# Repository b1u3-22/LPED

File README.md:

# LPED

Highly customizable Low-power Electronic Playing Dice

> This project started as a bachelors thesis, the original repository can be found [here](https://git.fit.vutbr.cz/xsedla2e/BP-LPED)

## Features

* Separate charging station for charging the dice via pogo-pins
* Changing the dice shape with custom sleeves 
* The dice can be configured to support any shape with up to 60 sides
* Up to 10 profiles can be saved onboard 

### Hardware 

* The dice uses a nRF52833 microcontroller with FXLS8974CF accelerometer
* Instead of battery it uses hybrid super-capacitor with 20 F capacity that provides up to 8 hours of game time with charging time of 15 minutes
* RGB LED on-board the dice
* The charger has separate battery providing up to two full dice charges
* The 3D models of the charging dock have been optimized for 3D printing and they do not require any supports
	* However, one heat inserts and 4 magnets (6x6x2mm) are necessary for the assembly

### Firmware 

* The dice transmits the landed numbers via BLE broadcast advertisement
	* To ensure they get to the client application, they are sent multiple times with unique identifier
* For configuration it is necessary to connect to the dice
	* It provides all the necessary parameters via characteristics in custom GATT service
* It saves the whole configuration in the FLASH memory of the dice, making it independent on the used client application
* Each side can have its own physical position on the dice and its own number, making it possible to create dice with custom non-standard shapes

## Project structure 
* `/hardware` - schematics, 3D models and PCB design files for dice, charger and programming adapter
	* The schematics and PCB designs were made in KiCad 
	* The printable models were made in FreeCAD 
* `/firmware` - Zephyr firmware running on the dice

## Versioning info 
* Repository uses `major.minor` format
	* `major` is incremented with each major hardware revision or significant firmware update that causes the implementation to be incompatible with previous version
	* `minor` is used for firmware fixes and patches that don't affect backwards compatibility
	* Branch names are created based on major revisions 
* PCBs have their own version code on them that follows standard `major.minor` format
	* `major` is used for drastic changes to the boards, such as MCU swap or change of pinout
	* `minor` is used for hardware fixes and patches

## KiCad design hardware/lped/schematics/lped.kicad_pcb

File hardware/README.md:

# Hardware designs 
* Schematic, PCB design files and used 3D models used in the design for the die, charging dock and programming adapter
* The `complete_bom.csv` contains BOM with components selected from Mouser

## Structure
1. `lped`
    * Design files for the die
2. `lped_dock`
    * Design files for for the modular charging station and single dice charging station
3. `lped_prog`
    * Design files for the programming adapter
2. `3d_models`
    * 3D models used in PCB design files in all three boards

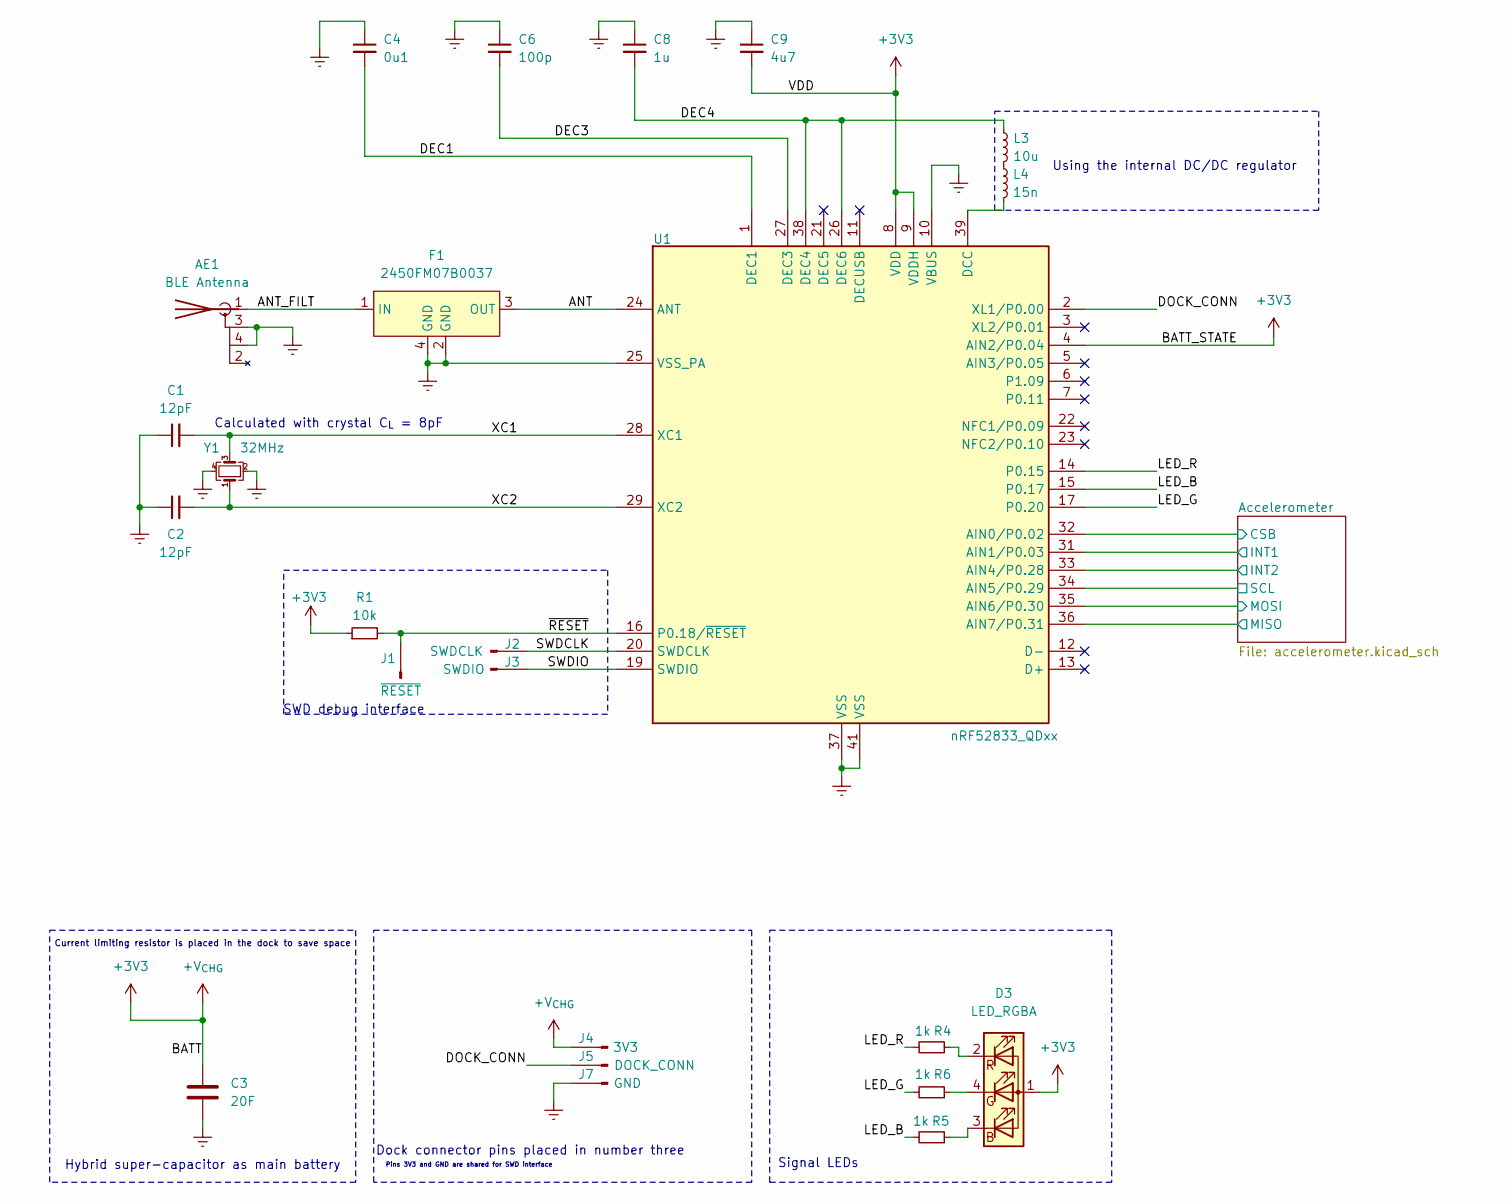
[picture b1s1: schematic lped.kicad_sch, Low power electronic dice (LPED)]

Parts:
AE1: BLE Antenna; XDCR_2450AT42E010BE
C1, C2: 12pF; C_0402_1005Metric
C3: 20F; C_Radial_D8.0mm_H11.5mm_P3.50mm
C4: 0u1; C_0402_1005Metric
C6: 100p; C_0402_1005Metric
C8: 1u; C_0603_1608Metric
C9: 4u7; C_0603_1608Metric
D3: LED_RGBA; LED_Wurth_150044M155260
F1: 2450FM07B0037; FIL_2450FM07D0034T
J1: ~{RESET}; TestPoint_Pad_D2.0mm
J2: SWDCLK; TestPoint_Pad_D2.0mm
J3: SWDIO; TestPoint_Pad_D2.0mm
J4: 3V3; TestPoint_Pad_D2.0mm
J5: DOCK_CONN; TestPoint_Pad_D2.0mm
J7: GND; TestPoint_Pad_2.0x2.0mm
L3: 10u; L_0603_1608Metric
L4: 15n; L_0402_1005Metric
R1: 10k; R_0402_1005Metric
R4, R5, R6: 1k; R_0402_1005Metric
U1: nRF52833_QDxx; QFN-40-1EP_5x5mm_P0.4mm_EP3.6x3.6mm
Y1: 32MHz; Crystal_SMD_2016-4Pin_2.0x1.6mm

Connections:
+3V3: C3.1, C9.2, D3.1 (A), J4.1, R1.1, U1.4 (AIN2/P0.04), U1.8 (VDD), U1.9 (VDDH), U1.18 (VDD), U1.30 (VDD), U1.40 (VDD); also elsewhere on the board
/ANT: F1.3 (OUT), U1.24 (ANT)
/ANT_FILT: AE1.1 (A), F1.1 (IN)
/Accelerometer/CSB: U1.32 (AIN0/P0.02); also elsewhere on the board
/Accelerometer/INT1: U1.31 (AIN1/P0.03); also elsewhere on the board
/Accelerometer/INT2: U1.33 (AIN4/P0.28); also elsewhere on the board
/Accelerometer/MISO: U1.36 (AIN7/P0.31); also elsewhere on the board
/Accelerometer/MOSI: U1.35 (AIN6/P0.30); also elsewhere on the board
/Accelerometer/SCL: U1.34 (AIN5/P0.29); also elsewhere on the board
/DEC1: C4.2, U1.1 (DEC1)
/DEC3: C6.2, U1.27 (DEC3)
/DEC4: C8.2, L3.1, U1.26 (DEC6), U1.38 (DEC4)
/DOCK_CONN: J5.1, U1.2 (XL1/P0.00)
/LED_B: R5.2, U1.15 (P0.17)
/LED_G: R6.2, U1.17 (P0.20)
/LED_R: R4.2, U1.14 (P0.15)
/SWDCLK: J2.1, U1.20 (SWDCLK)
/SWDIO: J3.1, U1.19 (SWDIO)
/XC1: C1.2, U1.28 (XC1), Y1.3
/XC2: C2.2, U1.29 (XC2), Y1.1
/~RESET: J1.1, R1.2, U1.16 (P0.18/~RESET)
Earth: AE1.3 (Shield), AE1.4 (Shield), C1.1, C2.1, C3.2, C4.1, C6.1, C8.1, C9.1, F1.2 (GND), F1.4 (GND), J7.1, U1.10 (VBUS), U1.25 (VSS_PA), U1.37 (VSS), U1.41 (VSS), Y1.2, Y1.4; also elsewhere on the board
unnamed: D3.3 (BK), R5.1
unnamed: D3.4 (GK), R6.1
unnamed: D3.2 (RK), R4.1
unnamed: L3.2, L4.1
unnamed: L4.2, U1.39 (DCC)

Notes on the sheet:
Calculated with crystal C_{L} = 8pF
SWD debug interface
Current limiting resistor is placed in the dock to save space
Signal LEDs
Dock connector pins placed in number three
Hybrid super-capacitor as main battery
Using the internal DC/DC regulator
Pins 3V3 and GND are shared for SWD interface

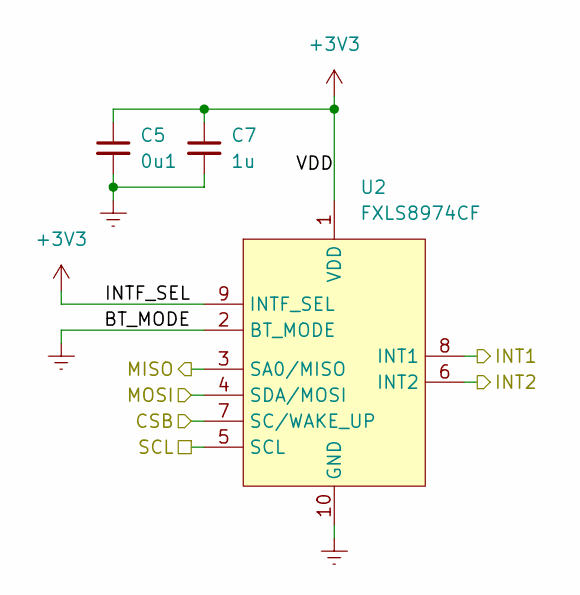
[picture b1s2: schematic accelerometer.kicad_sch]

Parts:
C5: 0u1; C_0402_1005Metric
C7: 1u; C_0402_1005Metric
U2: FXLS8974CF; DFN-10_2x2mm_P0.4mm

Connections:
+3V3: C5.1, C7.1, U2.1 (VDD), U2.9 (INTF_SEL); also elsewhere on the board
/Accelerometer/CSB: U2.7 (SC/WAKE_UP); also elsewhere on the board
/Accelerometer/INT1: U2.8 (INT1); also elsewhere on the board
/Accelerometer/INT2: U2.6 (INT2); also elsewhere on the board
/Accelerometer/MISO: U2.3 (SA0/MISO); also elsewhere on the board
/Accelerometer/MOSI: U2.4 (SDA/MOSI); also elsewhere on the board
/Accelerometer/SCL: U2.5 (SCL); also elsewhere on the board
Earth: C5.2, C7.2, U2.2 (BT_MODE), U2.10 (GND); also elsewhere on the board

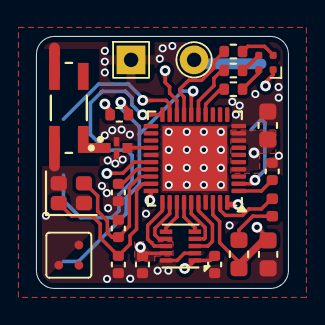
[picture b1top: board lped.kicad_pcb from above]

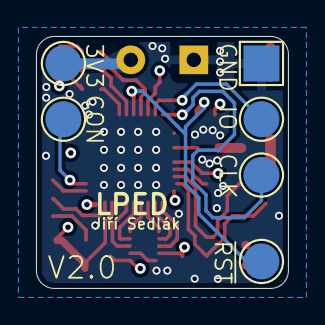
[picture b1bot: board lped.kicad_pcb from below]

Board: 4 copper layers, 14.0 x 14.0 mm, 27 parts (6 on the bottom side), 27 nets.

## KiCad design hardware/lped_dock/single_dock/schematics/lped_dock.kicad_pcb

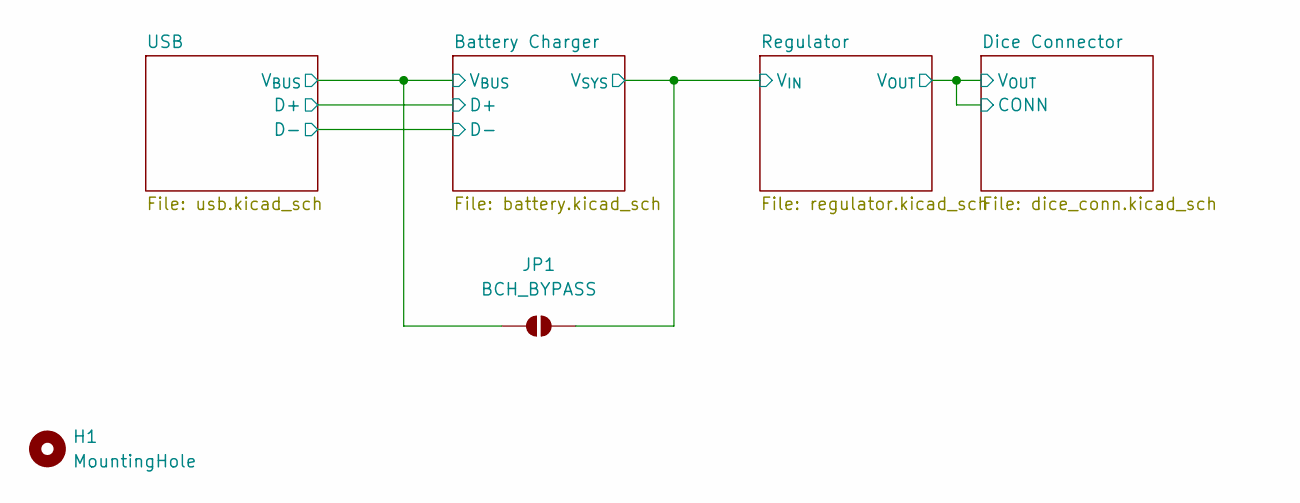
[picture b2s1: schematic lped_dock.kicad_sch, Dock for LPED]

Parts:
H1: MountingHole; MountingHole_3.2mm_M3
JP1: BCH_BYPASS; SolderJumper-2_P1.3mm_Open_Pad1.0x1.5mm

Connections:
/Battery Charger/V_{BUS}: JP1.1 (A); also elsewhere on the board
/Battery Charger/V_{SYS}: JP1.2 (B); also elsewhere on the board

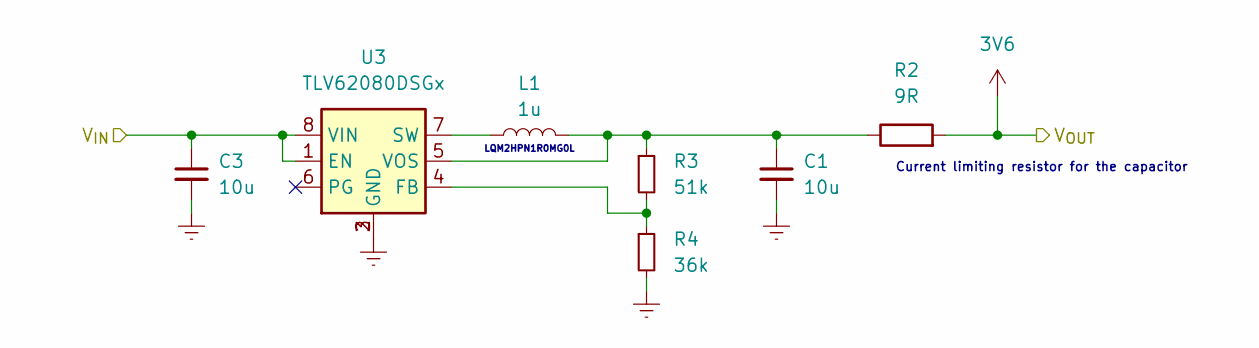
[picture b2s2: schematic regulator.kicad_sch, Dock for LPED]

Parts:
C1, C3: 10u; C_0603_1608Metric
L1: 1u; L_1008_2520Metric
R2: 9R; R_2512_6332Metric
R3: 51k; R_0402_1005Metric
R4: 36k; R_0402_1005Metric
U3: TLV62080DSGx; WSON-8-1EP_2x2mm_P0.5mm_EP0.9x1.6mm

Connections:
3V6: R2.2; also elsewhere on the board
/Battery Charger/V_{SYS}: C3.1, U3.1 (EN), U3.8 (VIN); also elsewhere on the board
Earth: C1.2, C3.2, R4.2, U3.2 (GND), U3.3 (GND), U3.9 (GND); also elsewhere on the board
unnamed: R3.2, R4.1, U3.4 (FB)
unnamed: L1.1, U3.7 (SW)
unnamed: C1.1, L1.2, R2.1, R3.1, U3.5 (VOS)

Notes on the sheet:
Current limiting resistor for the capacitor
LQM2HPN1R0MG0L

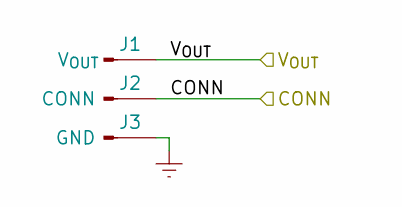
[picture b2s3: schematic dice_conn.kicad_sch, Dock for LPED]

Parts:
J1: V_{OUT}; Pin_D0.9mm_L10.0mm_W2.4mm_FlatFork
J2: CONN; Pin_D0.9mm_L10.0mm_W2.4mm_FlatFork
J3: GND; Pin_D0.9mm_L10.0mm_W2.4mm_FlatFork

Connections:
3V6: J1.1, J2.1; also elsewhere on the board
Earth: J3.1; also elsewhere on the board

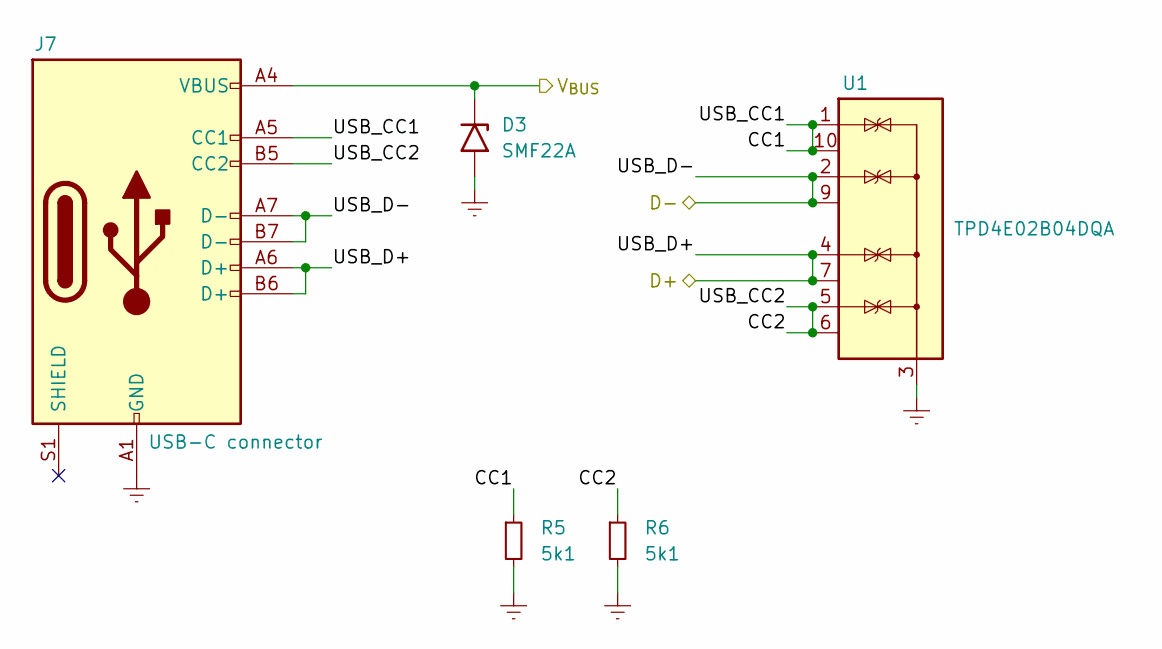
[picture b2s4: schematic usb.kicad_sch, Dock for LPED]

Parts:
D3: SMF22A; D_SOD-123
J7: USB-C connector; USB_C_Receptacle_GCT_USB4105-xx-A_16P_TopMnt_Horizontal
R5, R6: 5k1; R_0402_1005Metric
U1: TPD4E02B04DQA; USON-10_2.5x1.0mm_P0.5mm

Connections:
/Battery Charger/V_{BUS}: D3.1 (A1), J7.A4 (VBUS), J7.A9 (VBUS), J7.B4 (VBUS), J7.B9 (VBUS); also elsewhere on the board
/USB/CC1: J7.A5 (CC1), R5.1, U1.1 (IO1), U1.10 (NC)
/USB/CC2: J7.B5 (CC2), R6.1, U1.5 (IO4), U1.6 (NC)
/USB/USB_D+: J7.A6 (D+), J7.B6 (D+), U1.4 (IO3), U1.7 (NC); also elsewhere on the board
/USB/USB_D-: J7.A7 (D-), J7.B7 (D-), U1.2 (IO2), U1.9 (NC); also elsewhere on the board
Earth: D3.2 (A2), J7.A1 (GND), J7.A12 (GND), J7.B1 (GND), J7.B12 (GND), R5.2, R6.2, U1.3 (G), U1.8 (G); also elsewhere on the board

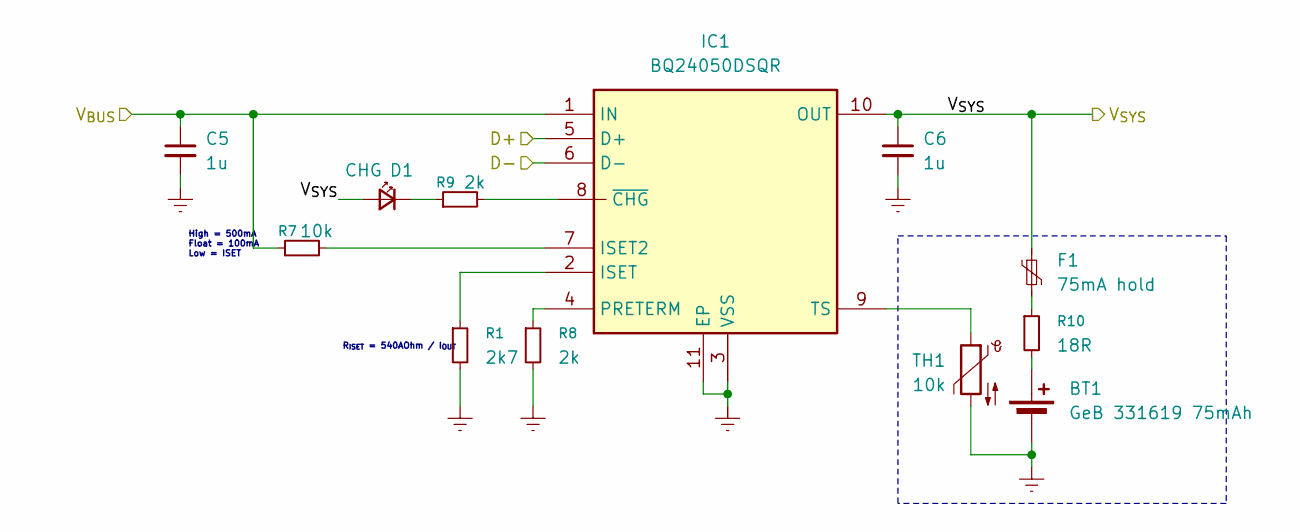
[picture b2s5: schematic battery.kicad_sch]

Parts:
BT1: GeB 331619 75mAh; JST_PH_S2B-PH-K_1x02_P2.00mm_Horizontal
C5, C6: 1u; C_0603_1608Metric
D1: CHG; LED_0805_2012Metric
F1: 75mA hold; Fuse_1206_3216Metric
IC1: BQ24050DSQR; SON40P200X200X80-11N; Manufacturer_Part_Number BQ24050DSQR; Mouser Part Number 595-BQ24050DSQR
R1: 2k7; R_0402_1005Metric
R7: 10k; R_0402_1005Metric
R8, R9: 2k; R_0402_1005Metric
R10: 18R; R_1206_3216Metric
TH1: 10k; R_0402_1005Metric

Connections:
/Battery Charger/V_{BUS}: C5.1, IC1.1 (IN), R7.1; also elsewhere on the board
/Battery Charger/V_{SYS}: C6.1, D1.2 (A), F1.1, IC1.10 (OUT); also elsewhere on the board
/USB/USB_D+: IC1.5 (D+); also elsewhere on the board
/USB/USB_D-: IC1.6 (D-); also elsewhere on the board
Earth: BT1.2 (-), C5.2, C6.2, IC1.3 (VSS), IC1.11 (EP), R1.2, R8.2, TH1.2; also elsewhere on the board
unnamed: BT1.1 (+), R10.2
unnamed: D1.1 (K), R9.1
unnamed: F1.2, R10.1
unnamed: IC1.7 (ISET2), R7.2
unnamed: IC1.2 (ISET), R1.1
unnamed: IC1.4 (PRETERM), R8.1
unnamed: IC1.9 (TS), TH1.1
unnamed: IC1.8 (~CHG), R9.2

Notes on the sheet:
High = 500mA Float = 100mA Low = ISET
R_{ISET} = 540AOhm / I_{OUT}

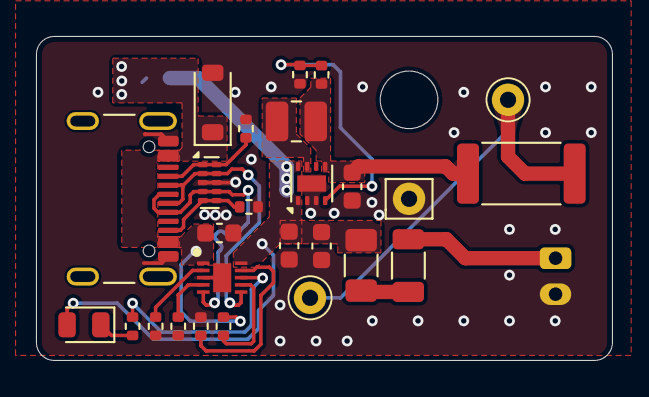
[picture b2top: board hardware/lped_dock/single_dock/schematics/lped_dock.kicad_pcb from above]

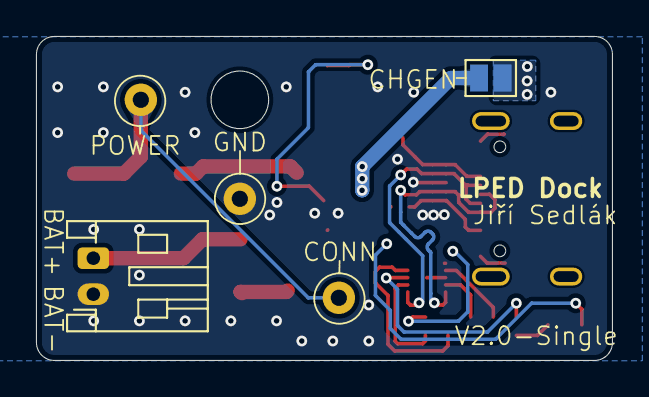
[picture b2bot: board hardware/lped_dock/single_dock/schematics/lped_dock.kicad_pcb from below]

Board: 2 copper layers, 32.0 x 18.0 mm, 29 parts (2 on the bottom side), 19 nets.

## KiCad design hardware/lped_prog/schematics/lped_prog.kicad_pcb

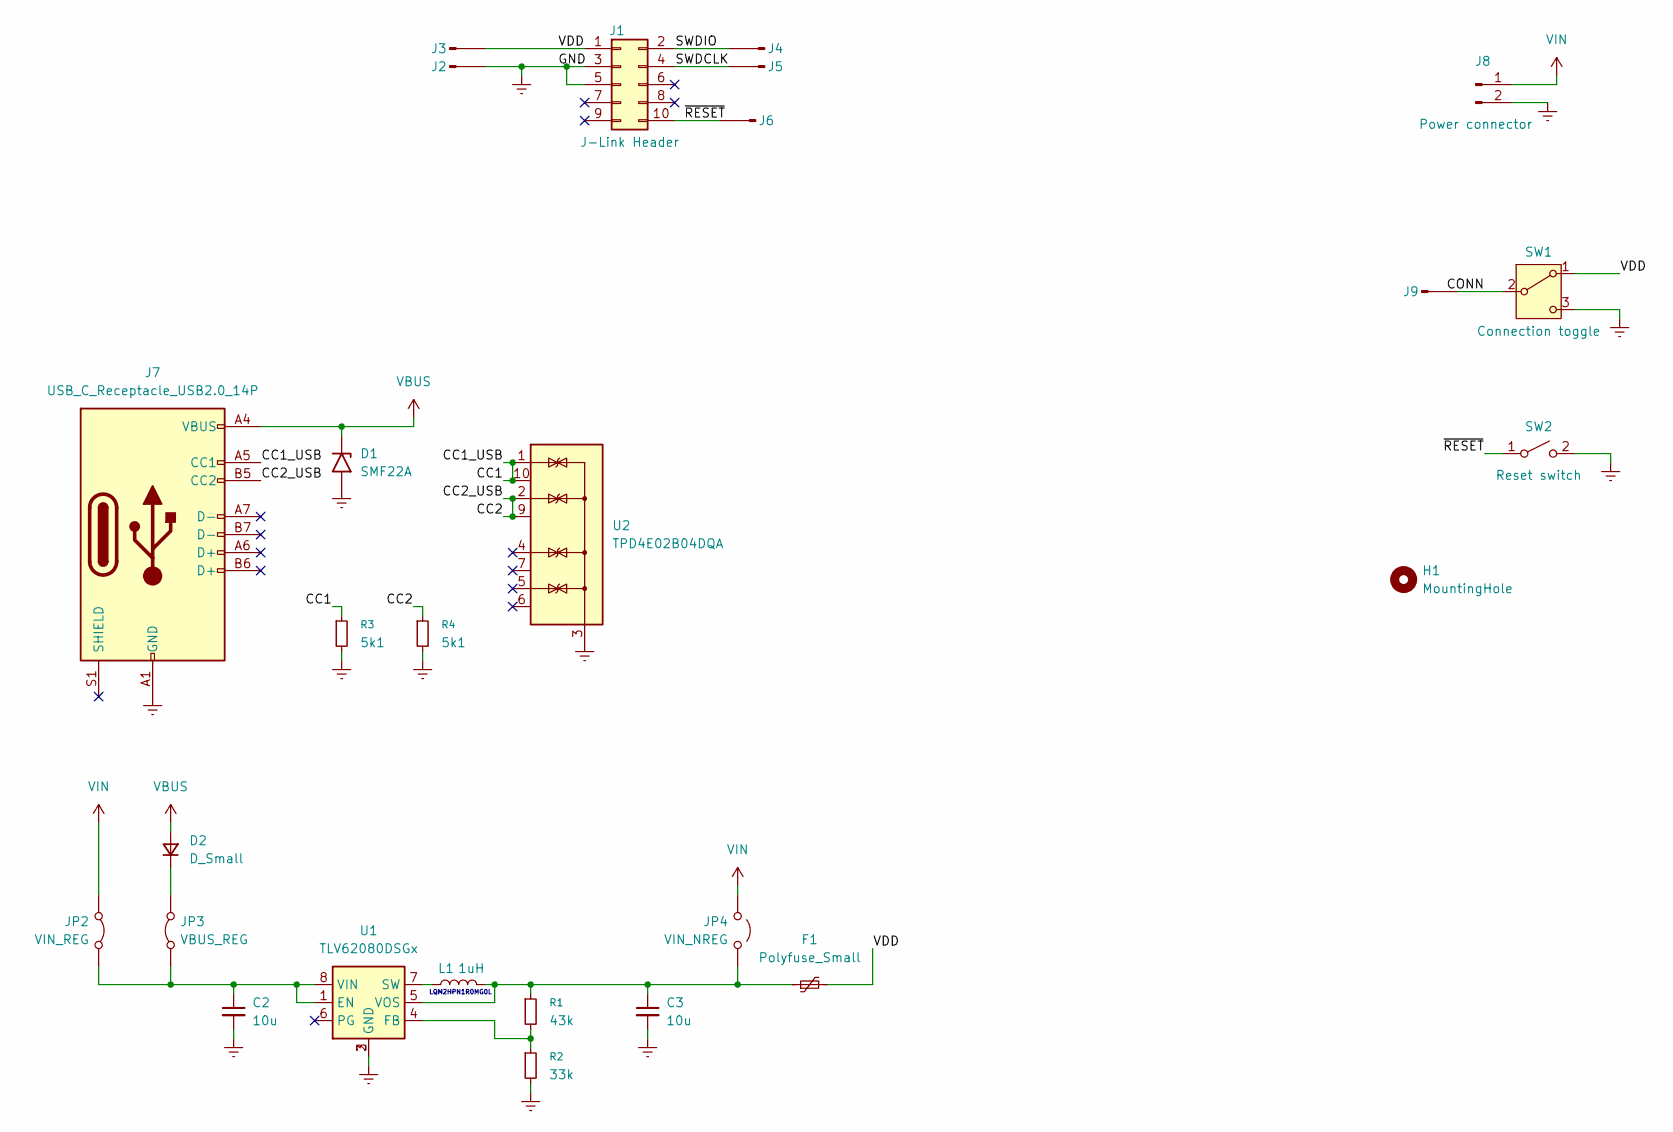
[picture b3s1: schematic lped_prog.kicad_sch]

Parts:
C2, C3: 10u; C_0603_1608Metric
D1: SMF22A; D_SMF
D2: D_Small; D_SOD-123F
F1: Polyfuse_Small; Fuse_1206_3216Metric
H1: MountingHole; MountingHole_3.2mm_M3
J1: J-Link Header; PinHeader_2x05_P1.27mm_Vertical_SMD
J2, J3, J4, J5, J6, J9: Conn_01x01_Pin; Pin_D0.9mm_L10.0mm_W2.4mm_FlatFork
J7: USB_C_Receptacle_USB2.0_14P; USB_C_Receptacle_GCT_USB4105-xx-A_16P_TopMnt_Horizontal
J8: Power connector; PinHeader_1x02_P2.54mm_Vertical
JP2: VIN_REG; PinHeader_1x02_P2.54mm_Vertical
JP3: VBUS_REG; PinHeader_1x02_P2.54mm_Vertical
JP4: VIN_NREG; PinHeader_1x02_P2.54mm_Vertical
L1: 1uH; L_1008_2520Metric
R1: 43k; R_0402_1005Metric
R2: 33k; R_0402_1005Metric
R3, R4: 5k1; R_0402_1005Metric
SW1: Connection toggle; EG1215AA
SW2: Reset switch; SW_PUSH_6mm_H4.3mm
U1: TLV62080DSGx; WSON-8-1EP_2x2mm_P0.5mm_EP0.9x1.6mm
U2: TPD4E02B04DQA; USON-10_2.5x1.0mm_P0.5mm

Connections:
/CC1: J7.A5 (CC1), R3.1, U2.1 (IO1), U2.10 (NC)
/CC2: J7.B5 (CC2), R4.1, U2.2 (IO2), U2.9 (NC)
/CONN: J9.1, SW1.2 (B)
/SWDCLK: J1.4, J5.1
/SWDIO: J1.2, J4.1
/VDD: F1.2, J1.1, J3.1, SW1.1 (A)
/~RESET: J1.10, J6.1, SW2.1 (A)
Earth: C2.2, C3.2, D1.2 (A2), J1.3, J1.5, J2.1, J7.A1 (GND), J7.A12 (GND), J7.B1 (GND), J7.B12 (GND), J8.2, R2.2, R3.2, R4.2, SW1.3 (C), SW2.2 (B), U1.2 (GND), U1.3 (GND), U1.9 (GND), U2.3 (G), U2.8 (G)
unnamed: D2.1 (K), JP3.2 (B)
unnamed: C2.1, JP2.1 (A), JP3.1 (A), U1.1 (EN), U1.8 (VIN)
unnamed: C3.1, F1.1, JP4.1 (A), L1.2, R1.1, U1.5 (VOS)
unnamed: R1.2, R2.1, U1.4 (FB)
unnamed: L1.1, U1.7 (SW)
VBUS: D1.1 (A1), D2.2 (A), J7.A4 (VBUS), J7.A9 (VBUS), J7.B4 (VBUS), J7.B9 (VBUS)
VIN: J8.1, JP2.2 (B), JP4.2 (B)

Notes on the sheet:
LQM2HPN1R0MG0L

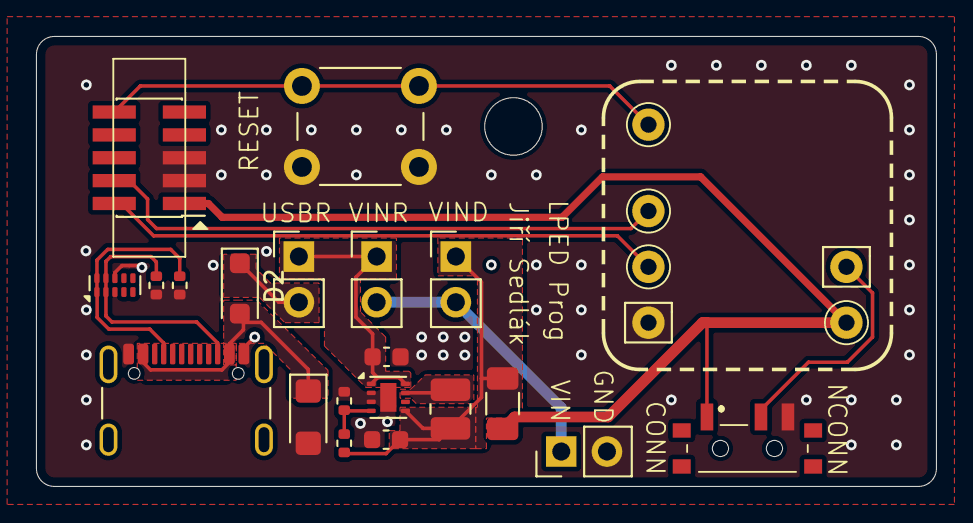
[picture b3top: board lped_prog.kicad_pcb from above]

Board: 2 copper layers, 50.0 x 25.0 mm, 27 parts (0 on the bottom side), 15 nets.

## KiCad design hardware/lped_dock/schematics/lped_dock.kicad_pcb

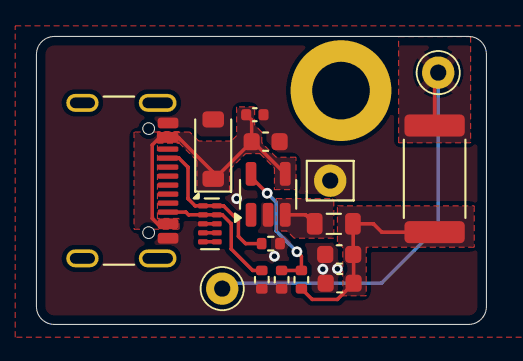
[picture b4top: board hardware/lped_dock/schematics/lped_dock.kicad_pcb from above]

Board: 2 copper layers, 25.0 x 16.0 mm, 18 parts (0 on the bottom side), 10 nets.

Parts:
C1, C2, C3: 10u; C_0603_1608Metric
C4: 0u1; C_0402_1005Metric
D3: SMF22A; D_SOD-123
H1: M3; MountingHole_3.2mm_M3_DIN965_Pad
J1: V_{OUT}; Pin_D0.9mm_L10.0mm_W2.4mm_FlatFork
J2: CONN; Pin_D0.9mm_L10.0mm_W2.4mm_FlatFork
J3: GND; Pin_D0.9mm_L10.0mm_W2.4mm_FlatFork
J7: USB-C connector; USB_C_Receptacle_GCT_USB4105-xx-A_16P_TopMnt_Horizontal
L1: 10u; L_0805_2012Metric
R2: 9R; R_2512_6332Metric
R3: 77k; R_0402_1005Metric
R4: 22k; R_0402_1005Metric
R5, R6: 5k1; R_0402_1005Metric
U1: TPD4E02B04DQA; USON-10_2.5x1.0mm_P0.5mm
U2: TPS560200; SOT-23-5

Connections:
3V6: J1.1, J2.1, R2.2
/Regulator/V_{IN}: C3.1, C4.1, D3.1 (A1), J7.A4 (VBUS), J7.A9 (VBUS), J7.B4 (VBUS), J7.B9 (VBUS), U2.4 (VIN)
/USB/CC1: J7.A5 (CC1), R5.1, U1.1 (IO1), U1.10 (NC)
/USB/CC2: J7.B5 (CC2), R6.1, U1.2 (IO2), U1.9 (NC)
/USB/D+: U1.5 (IO4), U1.6 (NC)
/USB/D-: U1.4 (IO3), U1.7 (NC)
Earth: C1.2, C2.2, C3.2, C4.2, D3.2 (A2), J3.1, J7.A1 (GND), J7.A12 (GND), J7.B1 (GND), J7.B12 (GND), R4.2, R5.2, R6.2, U1.3 (G), U1.8 (G), U2.2 (GND)
unnamed: C1.1, C2.1, L1.2, R2.1, R3.1
unnamed: R3.2, R4.1, U2.5 (FB)
unnamed: L1.1, U2.3 (PH)

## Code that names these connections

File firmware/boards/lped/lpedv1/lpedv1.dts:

/dts-v1/;
#include <nordic/nrf52810_qfaa.dtsi>
#include "lpedv1-pinctrl.dtsi"

/ {
	model = "LPEDv1 board";
	compatible = "lped,lpedv1";

	chosen {
		zephyr,sram = &sram0;
		zephyr,flash = &flash0;
		zephyr,code-partition = &slot0_partition;
	};

	leds {
		compatible = "gpio-leds";
		diceled: dice_led {
			gpios = <&gpio0 6 (1 << 9)>;
			label = "Dice LED";
		};

		dockled: dock_led {
			gpios = <&gpio0 5 (1 << 9)>;
			label = "Dock LED";
		};
	};

	inputs: zephyr,user {
		dock_conn-gpios = <&gpio0 4 GPIO_PULL_DOWN>;
		io-channels = <&adc 0>;
	};

	buttons {
		compatible = "gpio-keys";
		dockbutton: dock_button {
			gpios = <&gpio0 9 GPIO_PULL_DOWN>;
			label = "dock_button";
		};
	};
};

&gpio0 {
	status = "okay";
};

&gpiote {
	status = "okay";
};

&spi0 {
	status = "okay";
	compatible = "nordic,nrf-spi";
	pinctrl-0 = <&spi0_default>;
	pinctrl-1 = <&spi0_sleep>;
	pinctrl-names = "default", "sleep";
	cs-gpios = <&gpio0 14 GPIO_ACTIVE_LOW>;
	fxls89xx: fxls89xx@0 {
		zephyr,pm-device-runtime-auto;
		compatible = "nxp,fxls89xx";
		reg = <0x0>;
		spi-max-frequency = <2000000>;
		int1-gpios = <&gpio0 12 GPIO_PULL_UP>;
		int2-gpios = <&gpio0 15 GPIO_PULL_UP>;
	};
};

&adc {
	status = "okay";
	#address-cells = <1>;
	#size-cells = <0>;
	channel@0 {
		reg = <0>;
		zephyr,gain = "ADC_GAIN_1_6";			// Gain of 1/6 with internal reference (0.6V) results in range of +-3.6V
		zephyr,reference = "ADC_REF_INTERNAL";
		zephyr,acquisition-time = <ADC_ACQ_TIME_DEFAULT>;
		zephyr,input-positive = <NRF_SAADC_AIN6>;
		zephyr,resolution = <12>;
	};
};


&flash0 {
	partitions {
		compatible = "fixed-partitions";
		#address-cells = <1>;
		#size-cells = <1>;

		boot_partition: partition@0 {
			label = "mcuboot";
			reg = <0x00000000 DT_SIZE_K(48)>;
		};

		slot0_partition: partition@c000 {
			label = "image-0";
			reg = <0x0000c000 DT_SIZE_K(56)>;
		};

		slot1_partition: partition@1a000 {
			label = "image-1";
			reg = <0x0001a000 DT_SIZE_K(56)>;
		};

		storage_partition: partition@28000 {
			label = "storage";
			reg = <0x00028000 DT_SIZE_K(32)>;
		};
	};
};

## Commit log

2025-06-25 chore: move to a new repo
2025-06-25 chore: add license
2025-07-20 fix(firmware): remove redundant 1g check
    Removed redundant condition that checks if sum of acceleration values are close to +-1g
2025-07-20 chore: move lped pcb model to dir
2025-07-20 feat(hardware)!: v2 of LPED PCB
    * Changed MCU to nRF52833 (from nRF52810)
    * Added second LED
    * Used specialized filter instead of discrete components for ANT
    * Removed unnecessary pull-down resistor from miso
    * Removed DOCK_BTN
2025-07-20 chore: add version info to readme
2025-07-20 feat(firmware): added board definition for v2
2025-07-22 feat(hardware): replaced LEDs on dice
    * Replaced two red LEDs with single RGB LED (LTRB37G-4R4S)
    * Added more ground vias
    * Removed DOCK_LED
2025-07-22 feat(hardware): remove unused parts from dock pcb
    * Removed LED from dock
    * Removed button from dock
    * Removed connection pins for LED and button
2025-07-23 feat(hardware): minor single dock improvements
    * Moved connection pins closer together
    * Added ground stiching
2025-07-23 chore: restructure dock dir
    * Created separated dirs for modular and single dock
2025-08-18 feat(hardware): add battery charger and connector to single charger
2025-08-19 feat(hardware): added usb and manual input to programmer, added reset button and connection switch
2025-08-19 feat(hardware): added stiching to programmer
2025-08-19 feat(hardware): chaged regulator
2025-08-19 fix(hardware): shrinked keep-out area under USB-C on programmer
2025-08-19 feat(hardware): change regulator, add mounting hole to single charger
2025-08-24 feat(hardware): improvements to dock battery system
    * Added current limiting resistor to battery
    * Added charging status LED
    * Changed side of battery connector
2025-08-24 fix(hardware): LPED PCB clean up
2025-09-09 chore(hardware): remove outdated BOM
2025-09-09 feat(hardware): add batt charger bypass solder jump
2025-09-09 docs: update readme
2025-09-21 fix(hardware): minor fixes before manufacturing
    Changed footprint of USB protection diode
    Changed footprint of Programmer fuse
2025-10-10 fix(firmware): remove unused target from cmake
2025-10-10 feat(firmware): add new configs for LEDs
2025-10-10 feat(firmware): add RGB LED to the v2 device tree
2025-10-10 feat(firmware): new system for controlling Dice LEDs
    * Added new system for RGB LED control
    * It uses a separate thread for running the LED effects based on given animation structures
    * Animations can hold up to 20 animation steps with varying colors that can be selected from pallete of 16
    * Each color has its own duration
    * Each animation has its own fade type (none - changes instantly, fast and slow have preselected fade speeds, grad changes the colors for the whole duration between two colors)
    * Removed dock LED and Button function - they are not used anymore
2025-10-11 feat(firmware): add support for BLE FOTA
2025-10-11 feat(firmware): add connection based communication
    Added new characteristic and indication for dice number
2025-10-11 feat(firmware): added battery service
2025-10-11 feat(firmware): map cap soc on-board
    TODO: add more accurate mapping, such as LUT
2025-10-12 feat(firmware): added debug option to disable accelerometer
2025-10-12 chore(firmware): add dts for debug board
2025-10-12 feat(firmware): add boot animation with kconfig option
2025-10-12 feat(firmware): changed dice def loading
    * Removed GATT char for the whole dice definition, since it now has over 4kB
    * Added new characteristic for selected side definition (write to select side def by index, read to get its data)
2025-10-13 feat(hardware): update dice 3d model for v2
2025-10-13 fix(firmware): fix behaviour when removed from dock
2025-10-14 fix(firmware): allow reading the dice number characteristic
2025-10-14 feat(firmware): added gatt char for manual animations
2025-10-14 fix(firmware): dice number are now notifications
2025-10-15 fix(firmware): increase nvs sector size
2025-10-15 fix(firmware): do not call disconnected after bonded times out
2025-10-15 fix(firmware): restore the original reboot command
2025-10-15 fix(firmware): decrease maximum number of sides to 20
    * Most dice types have at most 20 sides
    * Bigger size of the dice_definition_t structure was causing issues with NVS read and write operations
2025-10-15 fix(firmware): restore original sector size
2025-10-15 fix(firmware): fix read and write storage functions for comm mode
2025-10-22 fix(firmware): increase sector count to fill available space
2025-10-22 fix(firmware): add static partitions
2025-10-22 chore(firmware): conf cleanup
2025-10-22 feat(firmware): add common anode kconfig option
2025-10-22 fix(firmware): remove visibility timeout kconfig option
2025-10-22 fix(firmware): use partition manager
2025-10-22 fix(firmware): fix led in lpedv2 device tree
2025-10-22 fix(firmware): fix vectors for 6-sided profile
2025-10-22 fix(firmware): fix set_led based on common anode option
2025-10-22 fix(firmware): use correct connected timeout, ignore EALREADY error from bt
2025-10-22 feat(hardware): new 3D models for dice
